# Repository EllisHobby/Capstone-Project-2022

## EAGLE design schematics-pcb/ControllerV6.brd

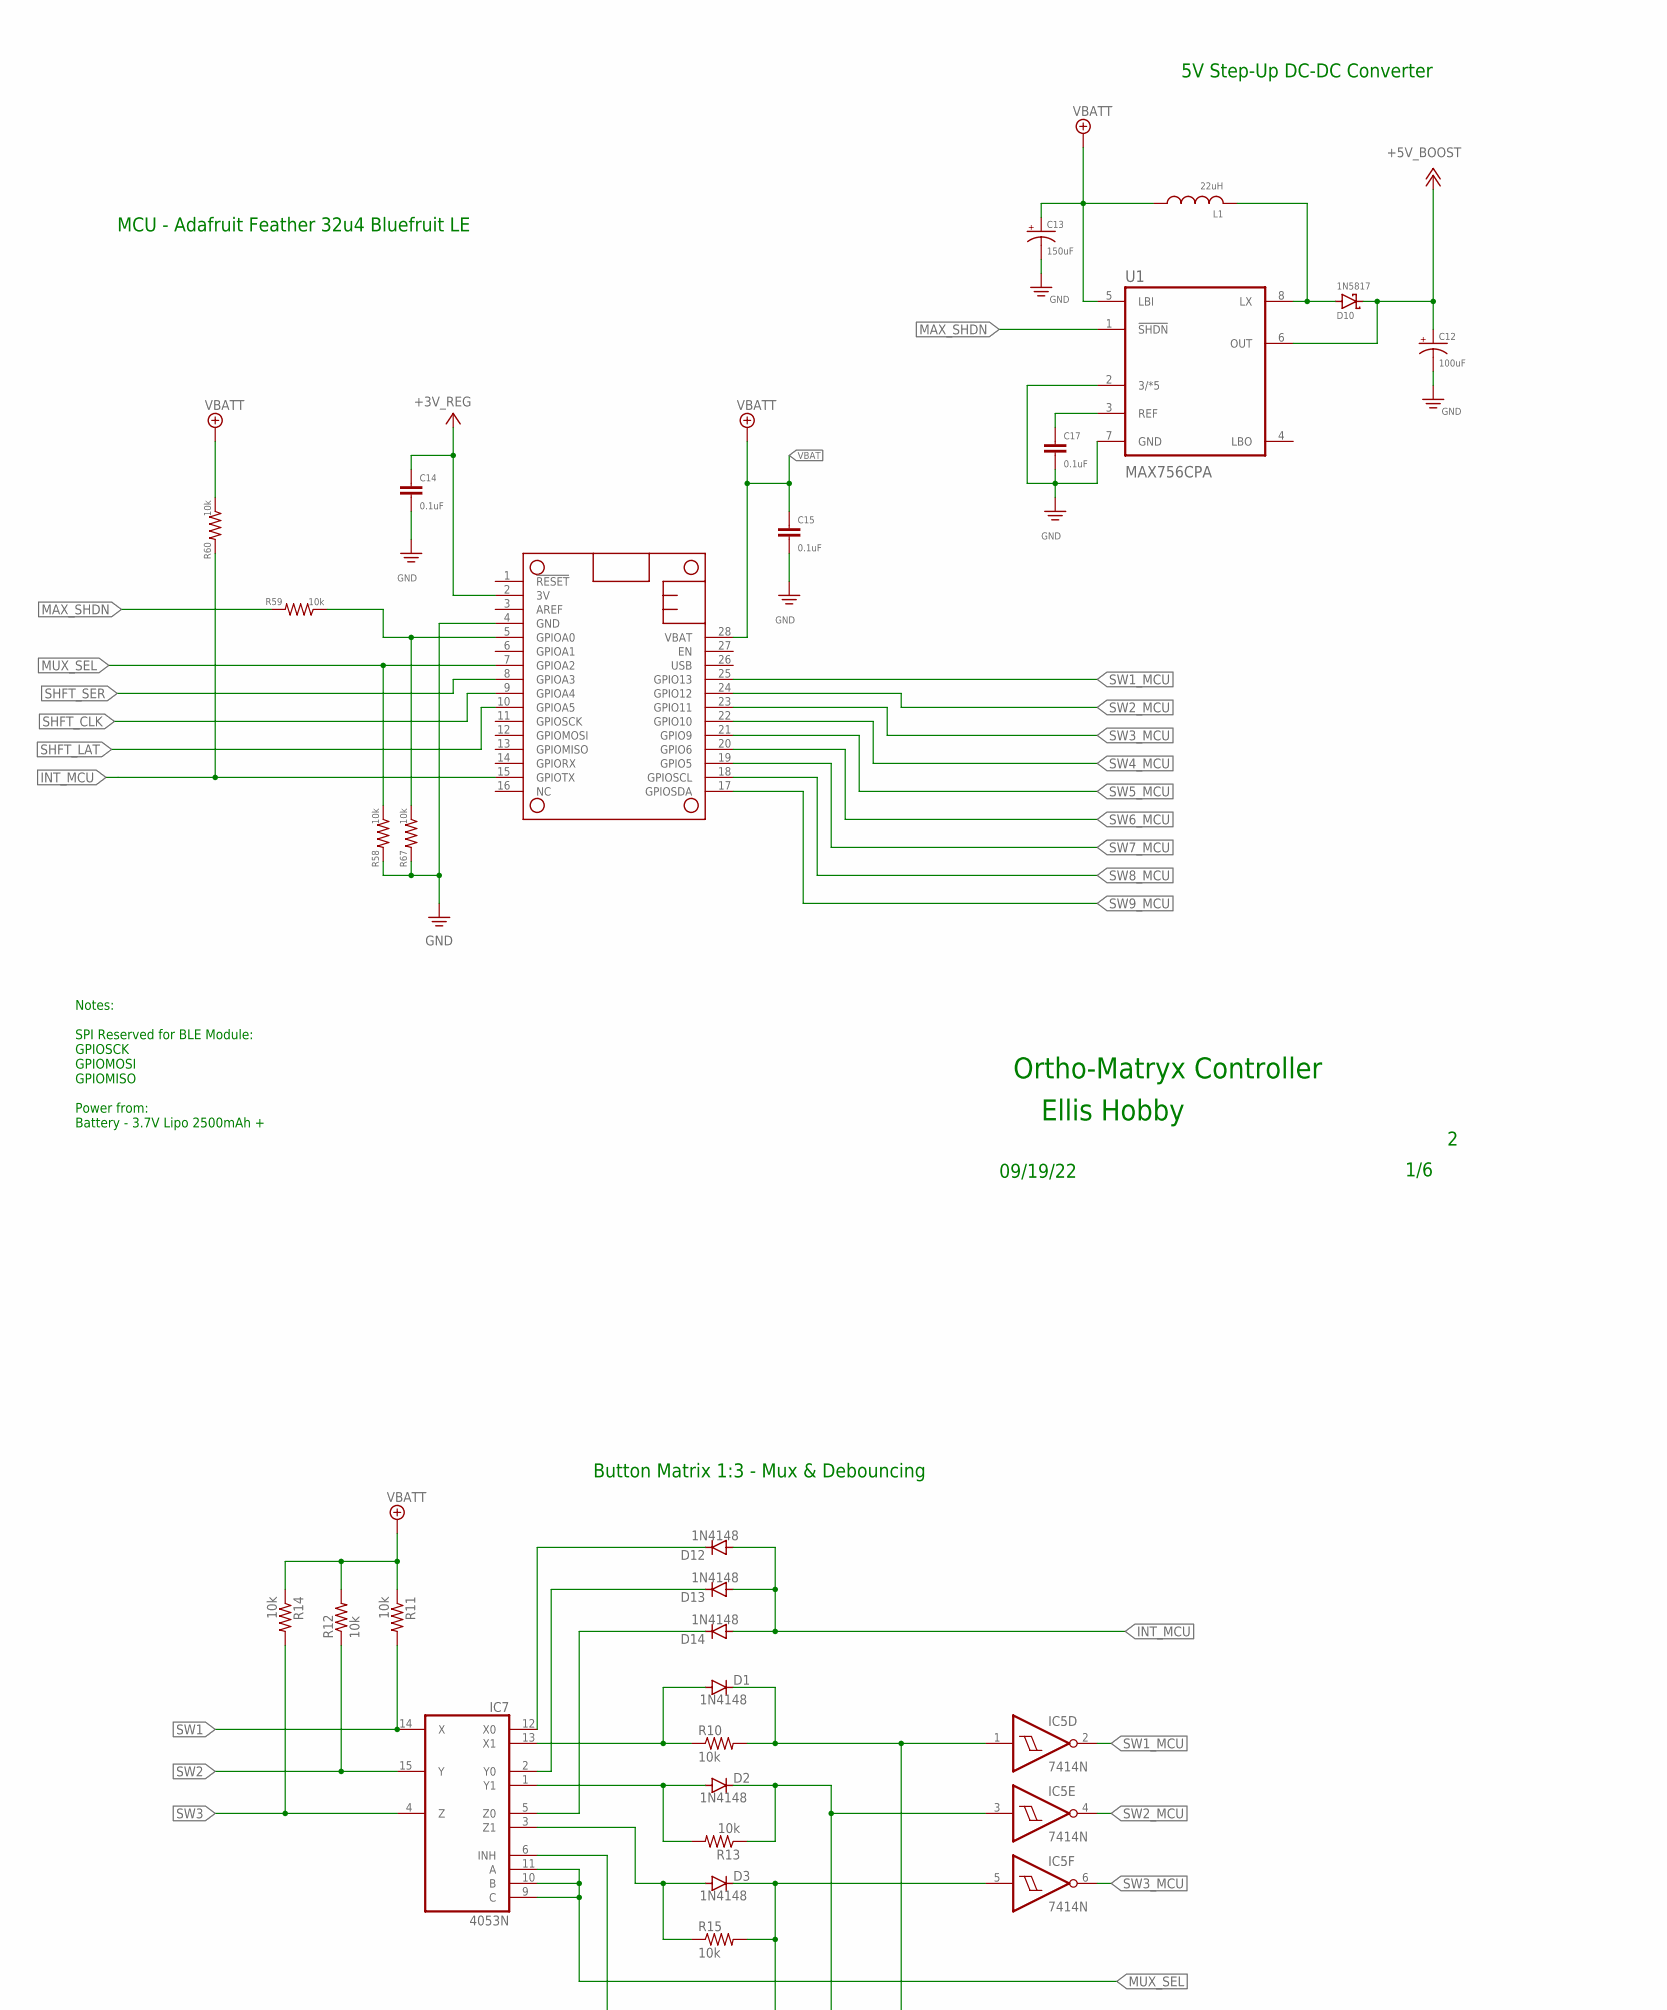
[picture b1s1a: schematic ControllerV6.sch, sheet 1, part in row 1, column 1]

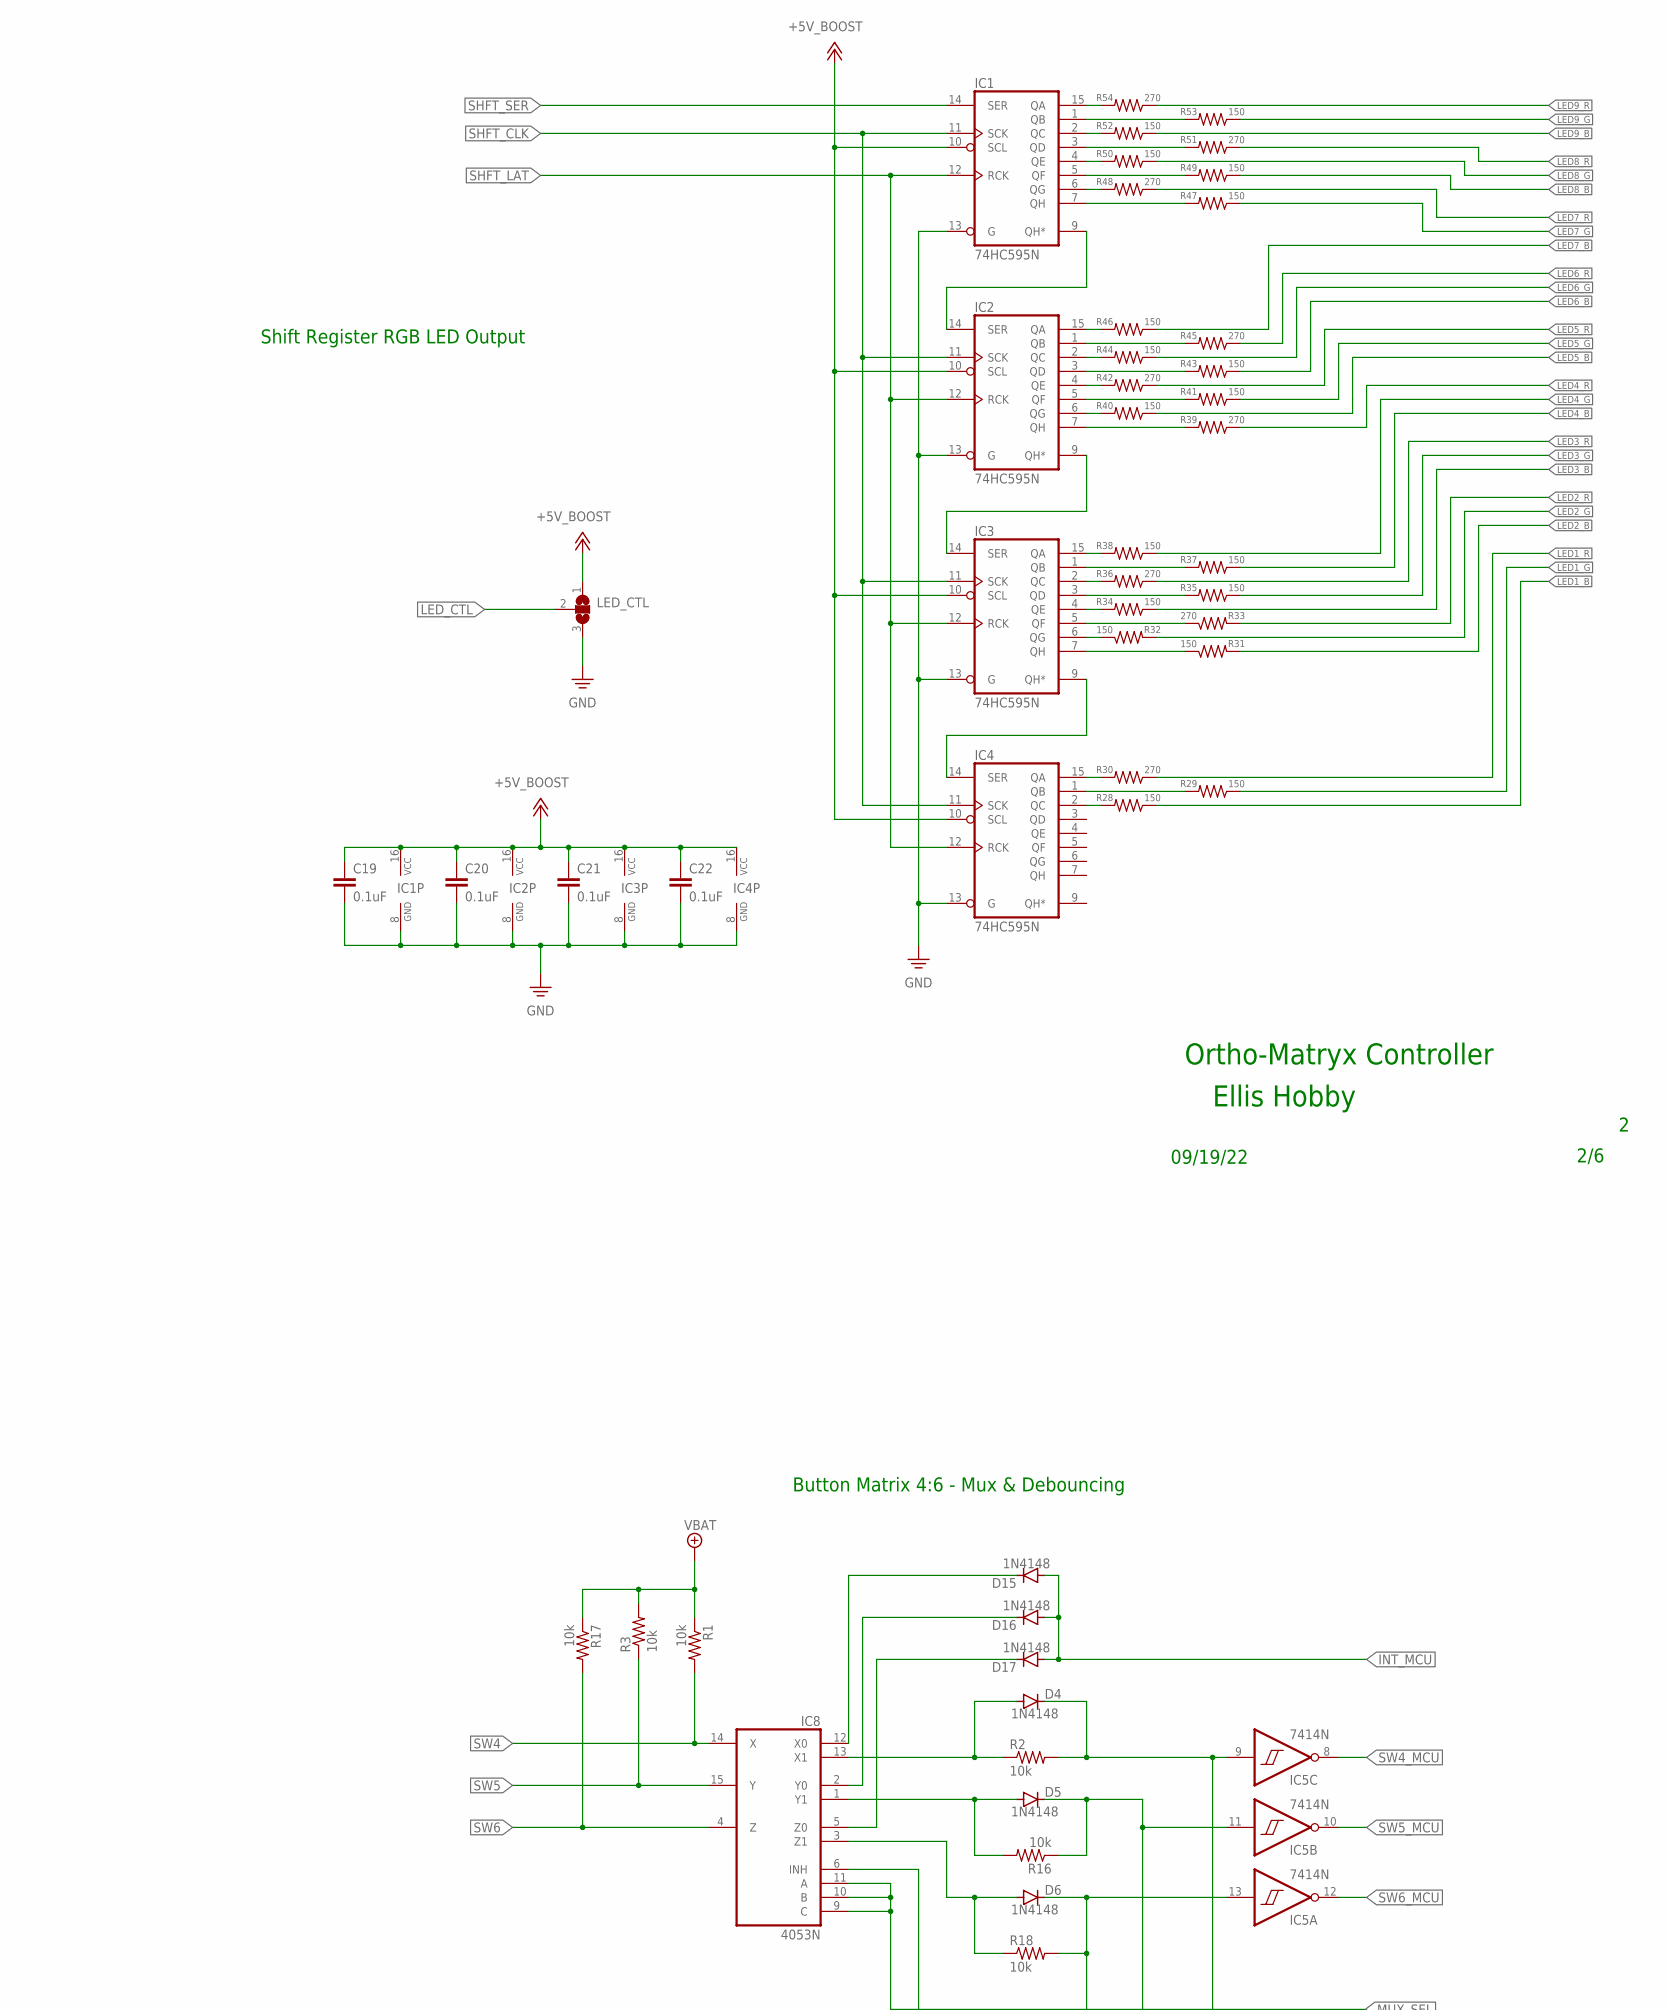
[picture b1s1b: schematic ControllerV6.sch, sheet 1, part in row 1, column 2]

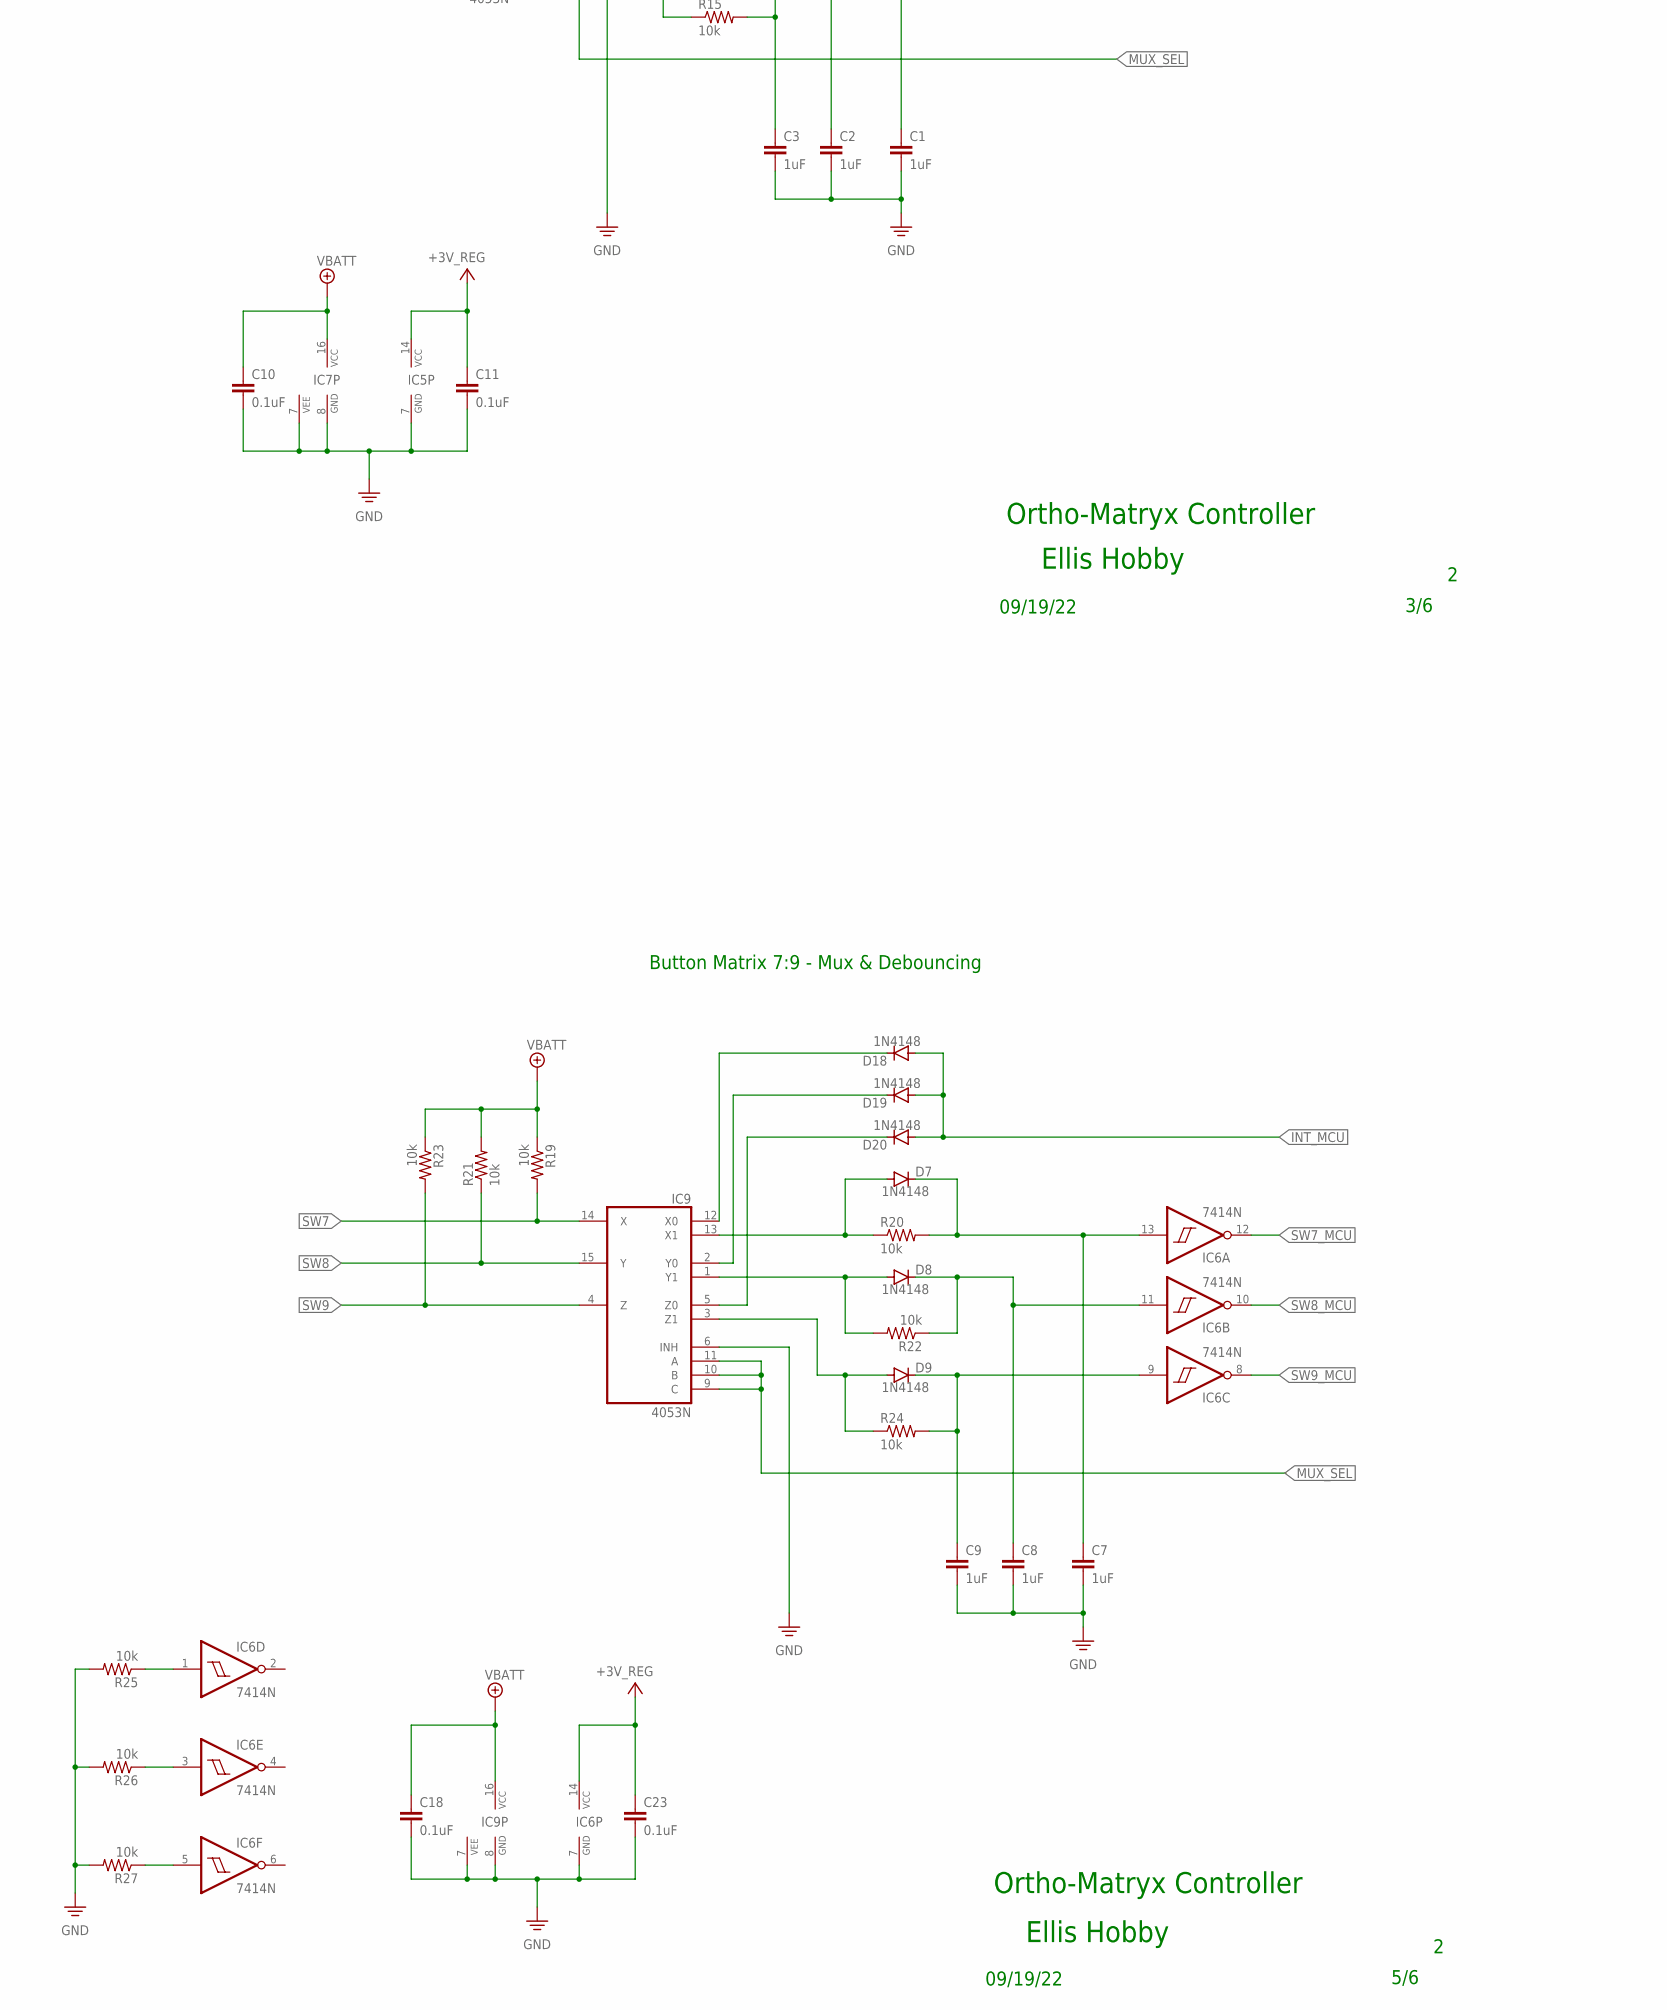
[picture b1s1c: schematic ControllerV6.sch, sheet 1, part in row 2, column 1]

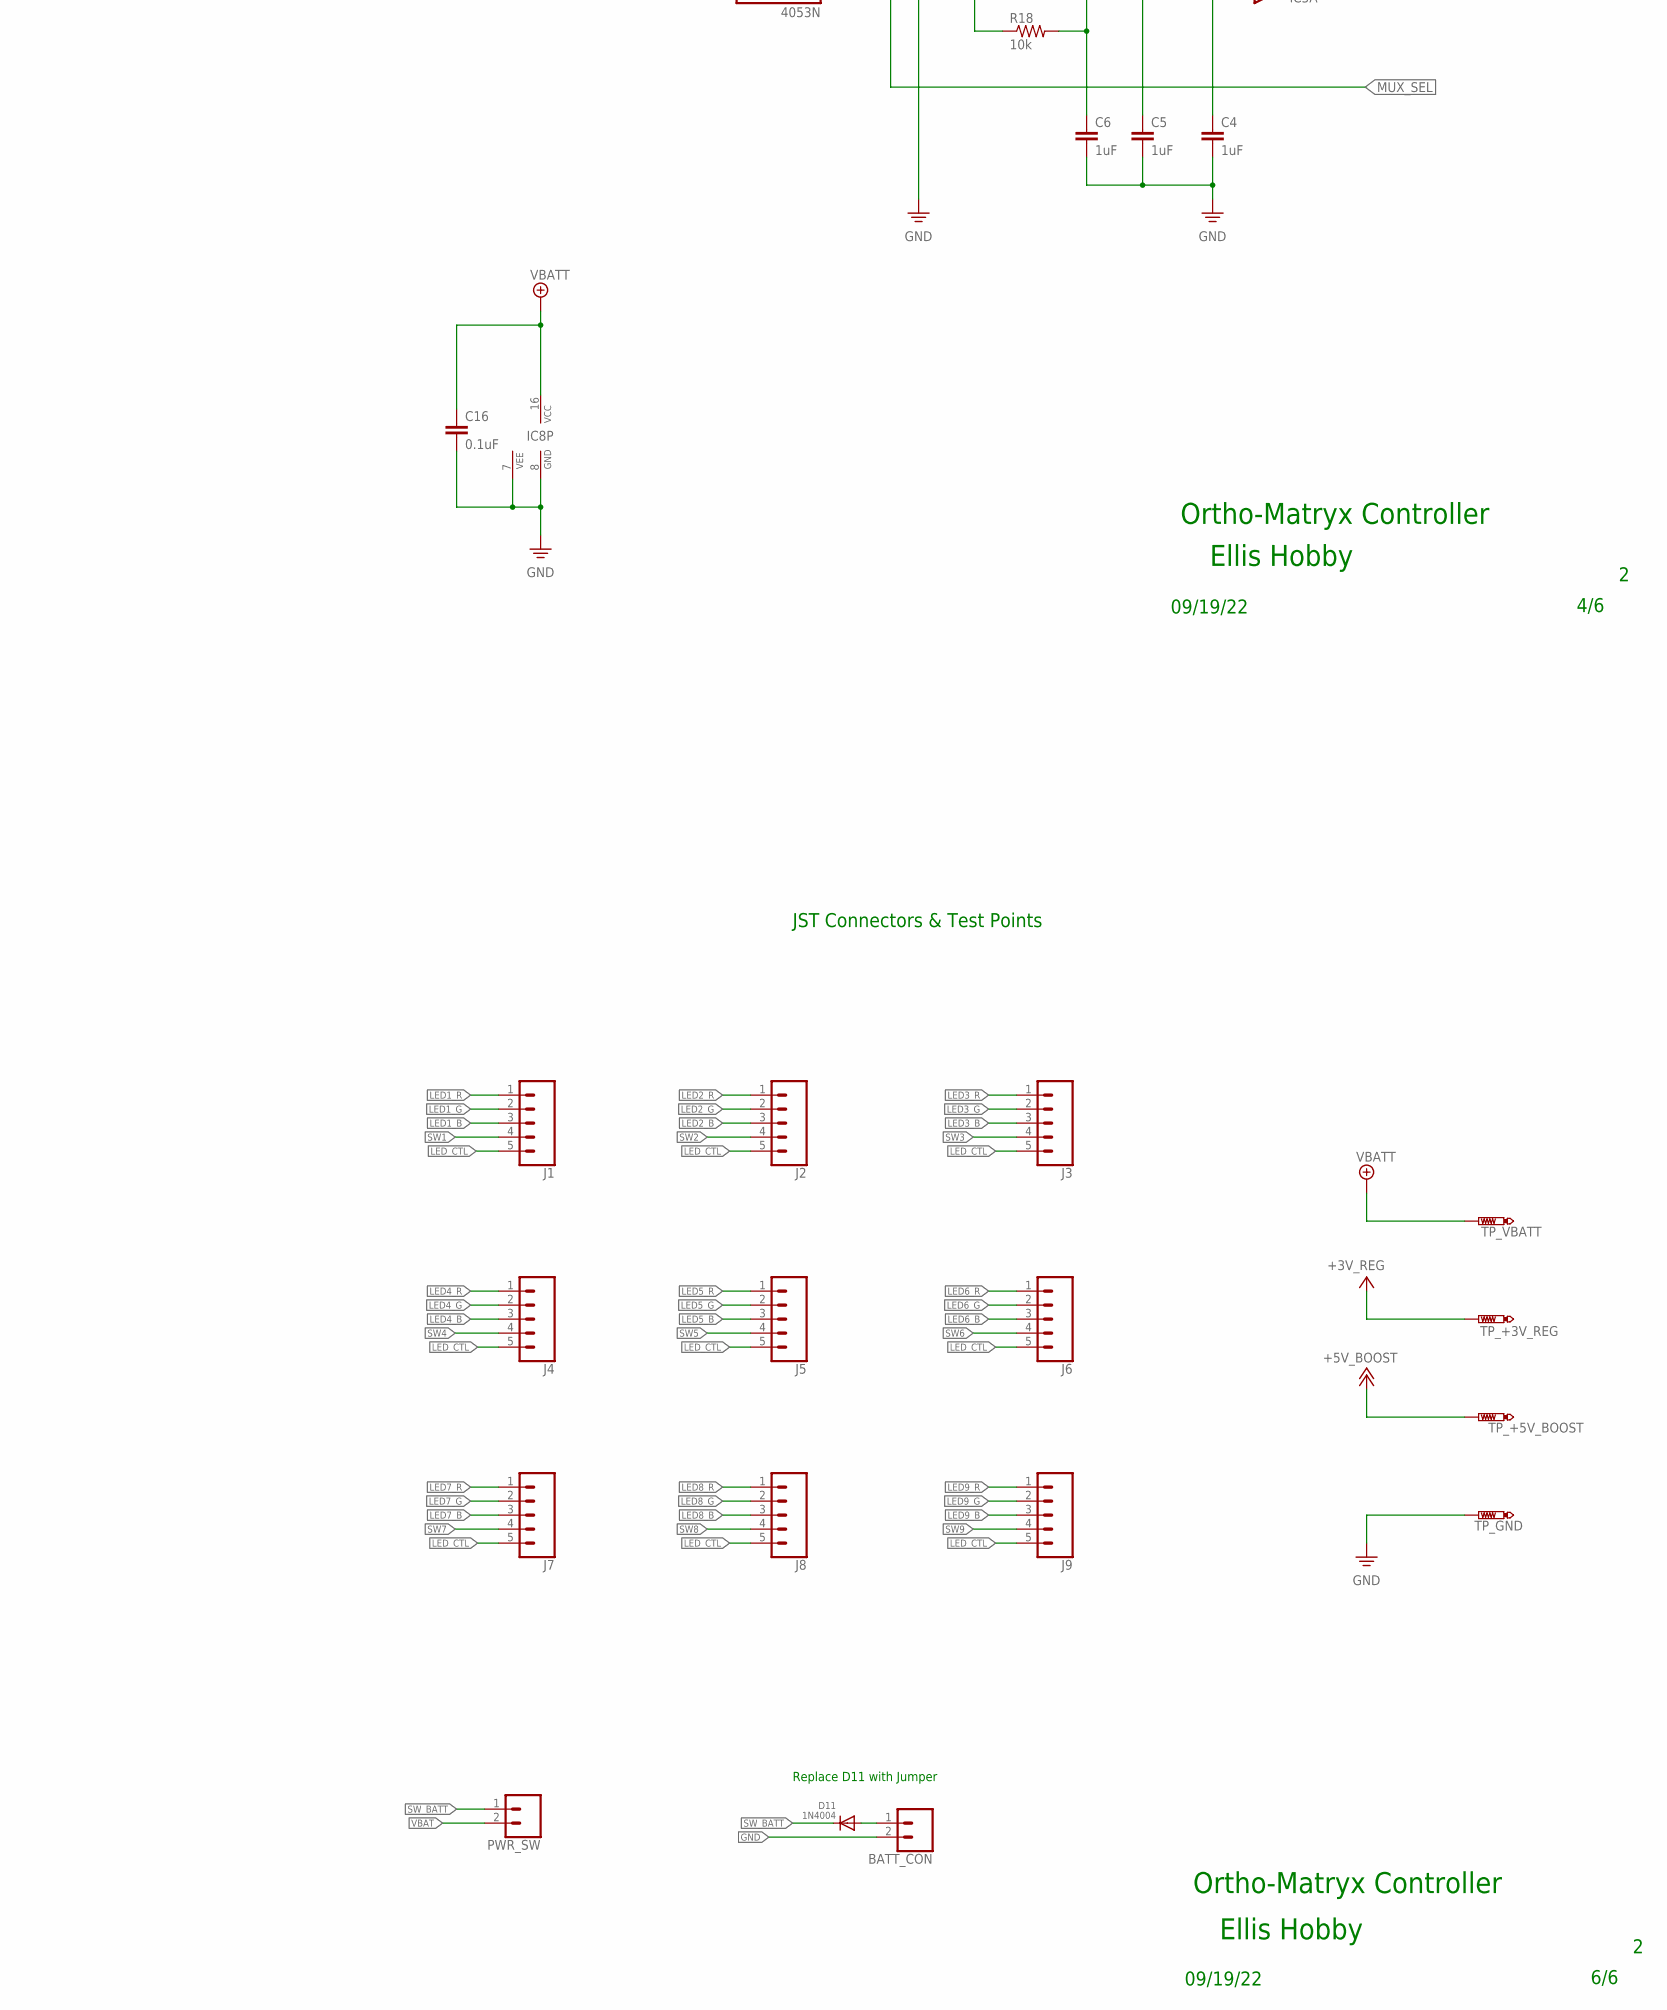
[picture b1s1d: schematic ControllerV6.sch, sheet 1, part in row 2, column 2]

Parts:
BATT_CON: CONN_02POLAR; MOLEX-1X2
C1, C2, C3, C4, C5, C6, C7, C8, C9: 1uF; C025-025X050
C10, C11, C14, C15, C16, C17, C18, C19, C20, C21, C22, C23: 0.1uF; C025-025X050
C12: 100uF; E1,8-4
C13: 150uF; E1,8-4
D1, D2, D3, D4, D5, D6, D7, D8, D9, D12, D13, D14, D15, D16, D17, D18, D19, D20: 1N4148; DO35-7
D10: 1N5817; DO41-7.6
D11: 1N4004; DO41-10
IC1, IC2, IC3, IC4: 74HC595N; DIL16
IC5, IC6: 7414N; DIL14
IC7, IC8, IC9: 4053N; DIL16
J1, J2, J3, J4, J5, J6, J7, J8, J9: CONN_05JST-VERT; JST-5-PTH-VERT
L1: 22uH; 0204/5
LED_CTL: SJ2WW; SJ_2W
MS2: FEATHERWING
PWR_SW: CONN_02POLAR; MOLEX-1X2
R1, R2, R3, R10, R11, R12, R13, R14, R15, R16, R17, R18, R19, R20, R21, R22, R23, R24, R25, R26, R27, R58, R59, R60, R67: 10k; 0204/5
R28, R29, R31, R32, R34, R35, R37, R38, R40, R41, R43, R44, R46, R47, R49, R50, R52, R53: 150; 0204/5
R30, R33, R36, R39, R42, R45, R48, R51, R54: 270; 0204/5
TP_+3V_REG, TP_+5V_BOOST: PTR1PAD1-13Y; P1-13Y
TP_GND: PTR1PAD1-13Y; P1-13Y
TP_VBATT: PTR1PAD1-13Y; P1-13Y
U1: MAX756CPA; DIP794W47P254L991H457Q8

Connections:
+3V_REG: C11.1, C14.1, C23.1, IC5.14 (VCC), IC6.14 (VCC), MS2.2 (3V), TP_+3V_REG.TP
+5V_BOOST: C12.+, C19.1, C20.1, C21.1, C22.1, D10.C, IC1.10 (SCL), IC1.16 (VCC), IC2.10 (SCL), IC2.16 (VCC), IC3.10 (SCL), IC3.16 (VCC), IC4.10 (SCL), IC4.16 (VCC), LED_CTL.1, TP_+5V_BOOST.TP, U1.6 (OUT)
D1: C1.1, D1.C, IC5.1 (I), R10.2
D2: C2.1, D2.C, IC5.3 (I), R13.1
D3: C3.1, D3.C, IC5.5 (I), R15.2
D4: C4.1, D4.C, IC5.9 (I), R2.2
D5: C5.1, D5.C, IC5.11 (I), R16.1
D6: C6.1, D6.C, IC5.13 (I), R18.2
D7: C7.1, D7.C, IC6.13 (I), R20.2
D8: C8.1, D8.C, IC6.11 (I), R22.1
D9: C9.1, D9.C, IC6.9 (I), R24.2
GND: BATT_CON.2, C1.2, C2.2, C3.2, C4.2, C5.2, C6.2, C7.2, C8.2, C9.2, C10.2, C11.2, C12.-, C13.-, C14.2, C15.2, C16.2, C17.2, C18.2, C19.2, C20.2, C21.2, C22.2, C23.2, IC1.8 (GND), IC1.13 (G), IC2.8 (GND), IC2.13 (G), IC3.8 (GND), IC3.13 (G), IC4.8 (GND), IC4.13 (G), IC5.7 (GND), IC6.7 (GND), IC7.6 (INH), IC7.7 (VEE), IC7.8 (GND), IC8.6 (INH), IC8.7 (VEE), IC8.8 (GND), IC9.6 (INH), IC9.7 (VEE), IC9.8 (GND), LED_CTL.3, MS2.4 (GND), R25.2, R26.2, R27.2, R58.2, R67.2, TP_GND.TP, U1.2 (3/*5), U1.7 (GND)
INT_MCU: D12.A, D13.A, D14.A, D15.A, D16.A, D17.A, D18.A, D19.A, D20.A, MS2.15 (GPIOTX), R60.2
LED1_B: J1.3, R28.1
LED1_G: J1.2, R29.1
LED1_R: J1.1, R30.1
LED2_B: J2.3, R31.2
LED2_G: J2.2, R32.2
LED2_R: J2.1, R33.2
LED3_B: J3.3, R34.1
LED3_G: J3.2, R35.1
LED3_R: J3.1, R36.1
LED4_B: J4.3, R37.1
LED4_G: J4.2, R38.1
LED4_R: J4.1, R39.1
LED5_B: J5.3, R40.1
LED5_G: J5.2, R41.1
LED5_R: J5.1, R42.1
LED6_B: J6.3, R43.1
LED6_G: J6.2, R44.1
LED6_R: J6.1, R45.1
LED7_B: J7.3, R46.1
LED7_G: J7.2, R47.1
LED7_R: J7.1, R48.1
LED8_B: J8.3, R49.1
LED8_G: J8.2, R50.1
LED8_R: J8.1, R51.1
LED9_B: J9.3, R52.1
LED9_G: J9.2, R53.1
LED9_R: J9.1, R54.1
LED_CTL: J1.5, J2.5, J3.5, J4.5, J5.5, J6.5, J7.5, J8.5, J9.5, LED_CTL.2
MAX_SHDN: R59.2, U1.1 (!SHDN)
MUX_SEL: IC7.9 (C), IC7.10 (B), IC7.11 (A), IC8.9 (C), IC8.10 (B), IC8.11 (A), IC9.9 (C), IC9.10 (B), IC9.11 (A), MS2.7 (GPIOA2), R58.1
unnamed: IC4.15 (QA), R30.2
unnamed: IC4.1 (QB), R29.2
unnamed: BATT_CON.1, D11.A
unnamed: D1.A, IC7.13 (X1), R10.1
unnamed: C17.1, U1.3 (REF)
unnamed: D13.C, IC7.2 (Y0)
unnamed: D14.C, IC7.5 (Z0)
unnamed: D2.A, IC7.1 (Y1), R13.2
unnamed: D16.C, IC8.2 (Y0)
unnamed: D12.C, IC7.12 (X0)
unnamed: D3.A, IC7.3 (Z1), R15.1
unnamed: D17.C, IC8.5 (Z0)
unnamed: D4.A, IC8.13 (X1), R2.1
unnamed: IC1.9 (QH*), IC2.14 (SER)
unnamed: IC2.9 (QH*), IC3.14 (SER)
unnamed: D5.A, IC8.1 (Y1), R16.2
unnamed: D15.C, IC8.12 (X0)
unnamed: D6.A, IC8.3 (Z1), R18.1
unnamed: D7.A, IC9.13 (X1), R20.1
unnamed: D8.A, IC9.1 (Y1), R22.2
unnamed: D9.A, IC9.3 (Z1), R24.1
unnamed: D18.C, IC9.12 (X0)
unnamed: D19.C, IC9.2 (Y0)
unnamed: D20.C, IC9.5 (Z0)
unnamed: IC4.2 (QC), R28.2
unnamed: IC1.15 (QA), R54.2
unnamed: IC3.9 (QH*), IC4.14 (SER)
unnamed: IC1.1 (QB), R53.2
unnamed: IC1.2 (QC), R52.2
unnamed: IC3.5 (QF), R33.1
unnamed: IC3.6 (QG), R32.1
unnamed: IC3.7 (QH), R31.1
unnamed: MS2.5 (GPIOA0), R59.1, R67.1
unnamed: IC1.3 (QD), R51.2
unnamed: IC1.4 (QE), R50.2
unnamed: IC1.5 (QF), R49.2
unnamed: IC3.4 (QE), R34.2
unnamed: IC3.2 (QC), R36.2
unnamed: IC3.3 (QD), R35.2
unnamed: IC1.6 (QG), R48.2
unnamed: IC1.7 (QH), R47.2
unnamed: IC2.15 (QA), R46.2
unnamed: IC2.1 (QB), R45.2
unnamed: IC2.2 (QC), R44.2
unnamed: IC2.3 (QD), R43.2
unnamed: IC2.4 (QE), R42.2
unnamed: IC2.6 (QG), R40.2
unnamed: IC2.7 (QH), R39.2
unnamed: IC3.15 (QA), R38.2
unnamed: IC3.1 (QB), R37.2
unnamed: IC2.5 (QF), R41.2
unnamed: IC6.1 (I), R25.1
unnamed: IC6.3 (I), R26.1
unnamed: IC6.5 (I), R27.1
unnamed: D10.A, L1.2, U1.8 (LX)
SHFT_CLK: IC1.11 (SCK), IC2.11 (SCK), IC3.11 (SCK), IC4.11 (SCK), MS2.9 (GPIOA4)
SHFT_LAT: IC1.12 (RCK), IC2.12 (RCK), IC3.12 (RCK), IC4.12 (RCK), MS2.10 (GPIOA5)
SHFT_SER: IC1.14 (SER), MS2.8 (GPIOA3)
SW1: IC7.14 (X), J1.4, R11.2
SW1_MCU: IC5.2 (O), MS2.25 (GPIO13)
SW2: IC7.15 (Y), J2.4, R12.1
SW2_MCU: IC5.4 (O), MS2.24 (GPIO12)
SW3: IC7.4 (Z), J3.4, R14.2
SW3_MCU: IC5.6 (O), MS2.23 (GPIO11)
SW4: IC8.14 (X), J4.4, R1.2
SW4_MCU: IC5.8 (O), MS2.22 (GPIO10)
SW5: IC8.15 (Y), J5.4, R3.1
SW5_MCU: IC5.10 (O), MS2.21 (GPIO9)
SW6: IC8.4 (Z), J6.4, R17.2
SW6_MCU: IC5.12 (O), MS2.20 (GPIO6)
SW7: IC9.14 (X), J7.4, R19.2
SW7_MCU: IC6.12 (O), MS2.19 (GPIO5)
SW8: IC9.15 (Y), J8.4, R21.1
SW8_MCU: IC6.10 (O), MS2.18 (GPIOSCL)
SW9: IC9.4 (Z), J9.4, R23.2
SW9_MCU: IC6.8 (O), MS2.17 (GPIOSDA)
SW_BATT: D11.C, PWR_SW.1
VBAT: C10.1, C13.+, C15.1, C16.1, C18.1, IC7.16 (VCC), IC8.16 (VCC), IC9.16 (VCC), L1.1, MS2.28 (VBAT), PWR_SW.2, R1.1, R3.2, R11.1, R12.2, R14.1, R17.1, R19.1, R21.2, R23.1, R60.1, TP_VBATT.TP, U1.5 (LBI)

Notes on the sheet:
Shift Register RGB LED Output
MCU - Adafruit Feather 32u4 Bluefruit LE
5V Step-Up DC-DC Converter
Notes: SPI Reserved for BLE Module: GPIOSCK GPIOMOSI GPIOMISO Power from: Battery - 3.7V Lipo 2500mAh +
Ortho-Matryx Controller
Ellis Hobby
09/19/22
1/6
2/6
3/6
6/6
4/6
5/6
Button Matrix 1:3 - Mux & Debouncing
Button Matrix 4:6 - Mux & Debouncing
Button Matrix 7:9 - Mux & Debouncing
JST Connectors & Test Points
Replace D11 with Jumper

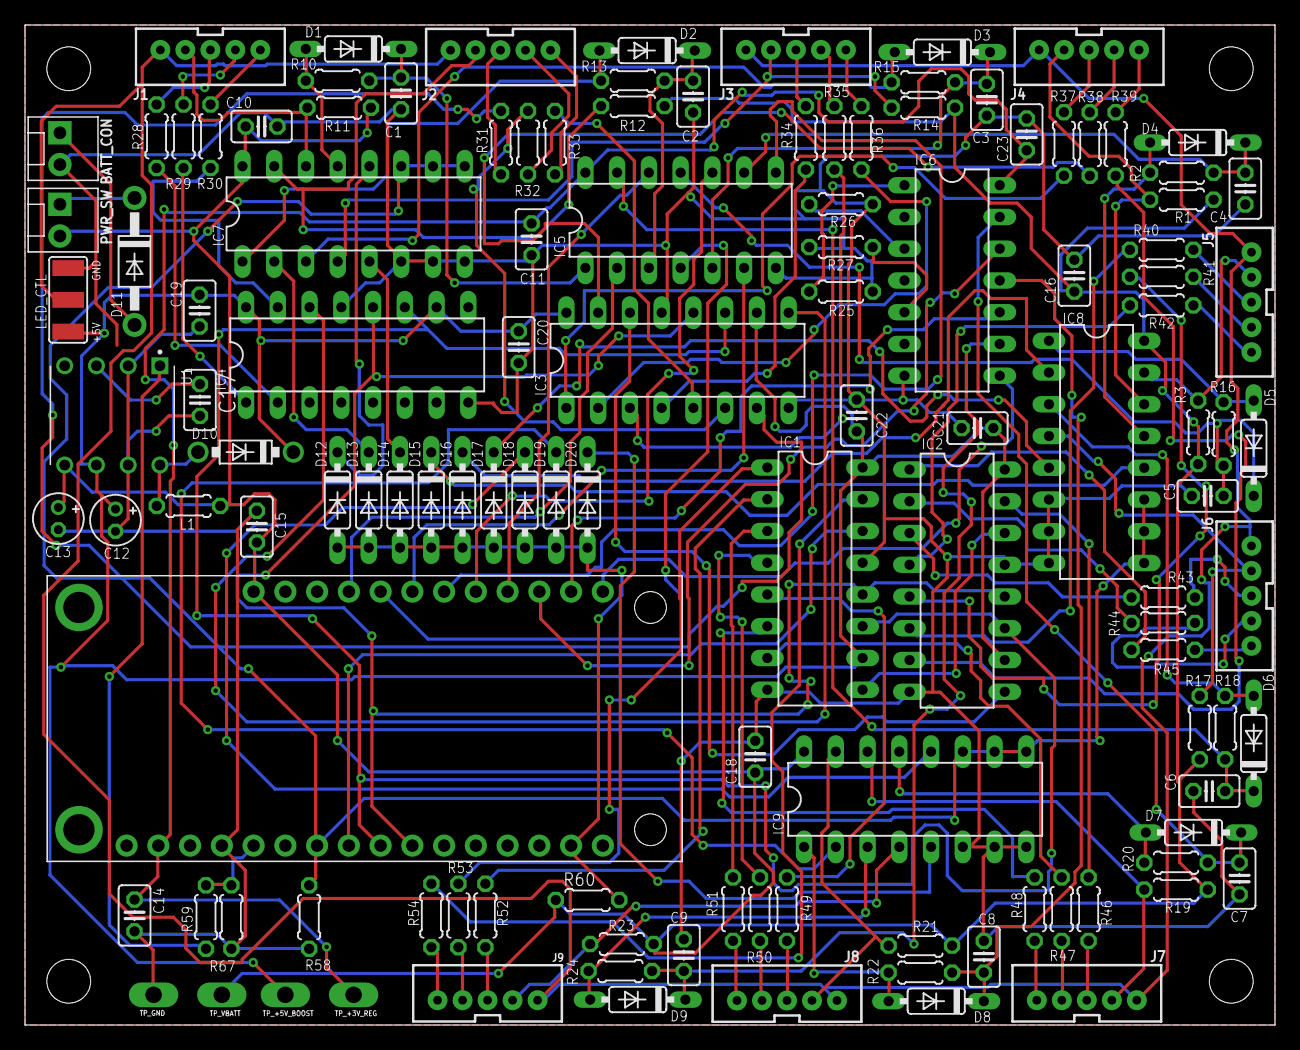
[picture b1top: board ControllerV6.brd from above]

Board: 2 copper layers, 100.0 x 80.0 mm, 123 parts (0 on the bottom side), 121 nets.

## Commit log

2022-12-01 Upload relevent files
2022-12-15 add achematics and pcb files
2022-12-15 add updated ble code
2022-12-15 add updated ble
2022-12-15 add updated ble and games

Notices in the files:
parts and their libraries:
SparkFun-Connectors: Licensing: Creative Commons ShareAlike 4.0 International - https://creativecommons.org/licenses/by-sa/4.0
